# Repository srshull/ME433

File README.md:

# ME433
Homework and other files for ME 433 - Advanced Mechatronics, which I completed in the Spring quarter of 2016 at Northwestern University. 

## Final Project
Here's a sneak peek at my final project - a line following robot. The camera on an Android phone detects the line, then communicates with a PIC32 microcontroller over USB. The PIC32 implements a proportional-integral controller to control the two motors in order to follow the line around a track. I designed the chassis, motor mounts, and wheels in Onshape and fabricated them using a laser cutter and 3D printer, respectively.

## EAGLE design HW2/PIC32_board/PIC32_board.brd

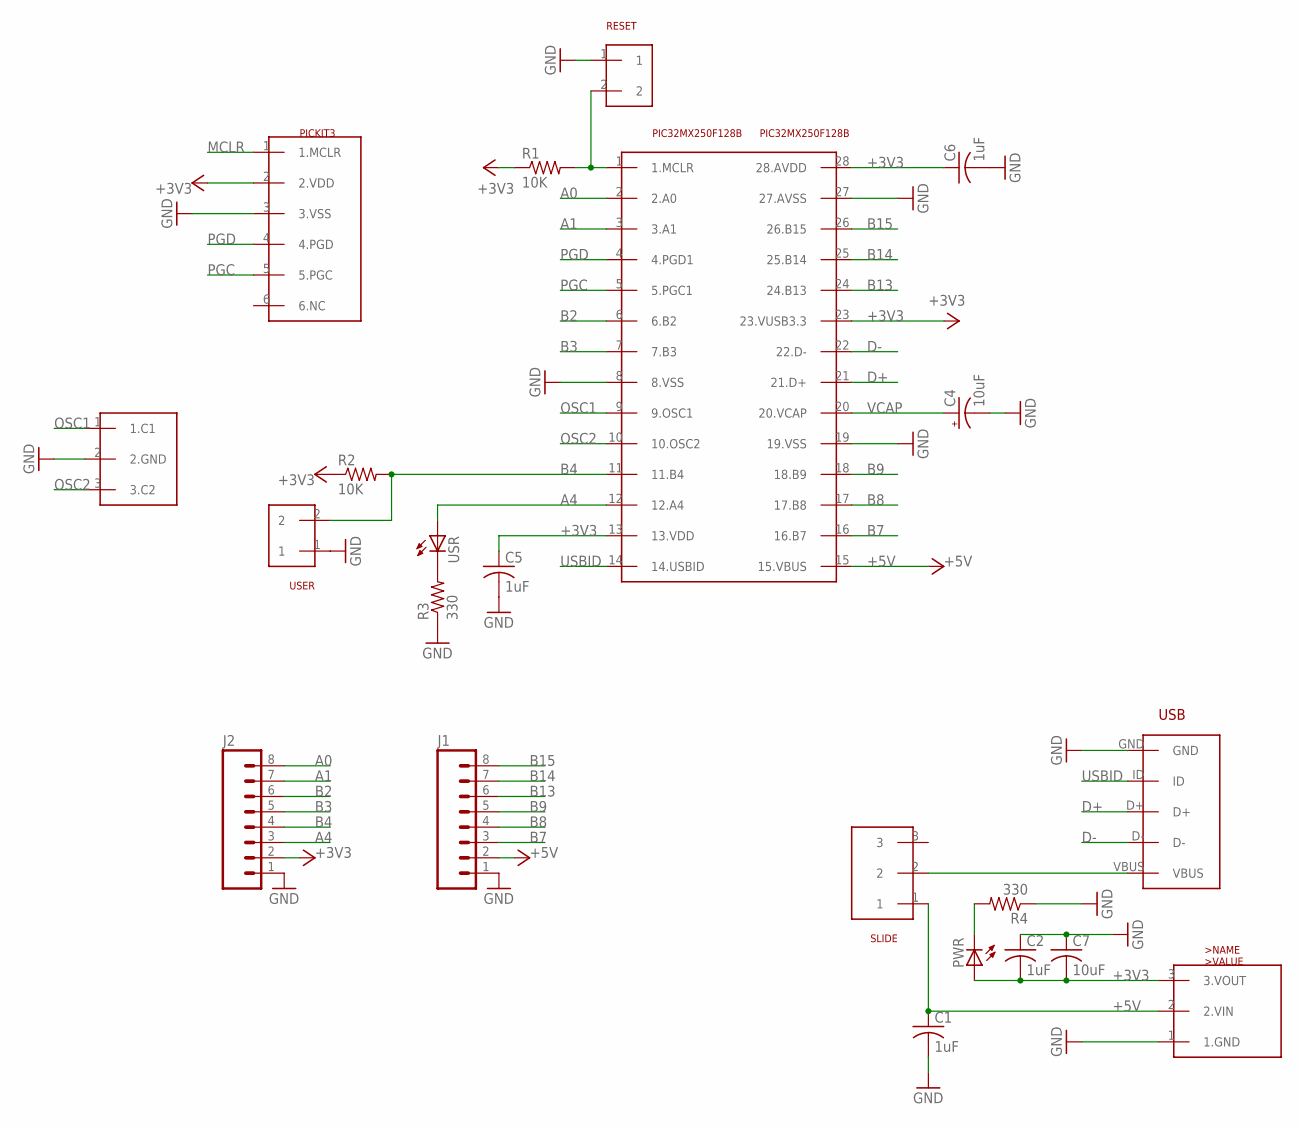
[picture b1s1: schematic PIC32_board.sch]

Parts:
C1, C2, C5, C6: 1uF; C025-024X044
C4: 10uF; B45181B
C7: 10uF; C025-024X044
J1, J2: M08; 1X08_ROUND
OSC: OSC; 1X03
PIC32MX250F128B: PIC32MX250F128B; DIL28-3
PICKIT3: PICKIT3; 1X06
PWR: LED3MM
R1, R2: 10K; 0207/10
R3, R4: 330; 0207/10
RESET: PUSHBUTTON
SLIDE: SLIDE
U$3: MCP1702; TO92
USB: USB_5PIN; USB-MB-H
USER: PUSHBUTTON
USR: LED3MM

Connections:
+3V3: C2.2, C5.1, C6.1, C7.2, J2.2, PIC32MX250F128B.13 (13.VDD), PIC32MX250F128B.23 (23.VUSB3.3), PIC32MX250F128B.28 (28.AVDD), PICKIT3.2 (2.VDD), PWR.A, R1.1, R2.1, U$3.3 (3.VOUT)
+5V: C1.1, J1.2, PIC32MX250F128B.15 (15.VBUS), SLIDE.1, U$3.2 (2.VIN)
A0: J2.8, PIC32MX250F128B.2 (2.A0)
A1: J2.7, PIC32MX250F128B.3 (3.A1)
A4: J2.3, PIC32MX250F128B.12 (12.A4), USR.A
B2: J2.6, PIC32MX250F128B.6 (6.B2)
B3: J2.5, PIC32MX250F128B.7 (7.B3)
B4: J2.4, PIC32MX250F128B.11 (11.B4), R2.2, USER.2
B7: J1.3, PIC32MX250F128B.16 (16.B7)
B8: J1.4, PIC32MX250F128B.17 (17.B8)
B9: J1.5, PIC32MX250F128B.18 (18.B9)
B13: J1.6, PIC32MX250F128B.24 (24.B13)
B14: J1.7, PIC32MX250F128B.25 (25.B14)
B15: J1.8, PIC32MX250F128B.26 (26.B15)
D+: PIC32MX250F128B.21 (21.D+), USB.D+
D-: PIC32MX250F128B.22 (22.D-), USB.D-
GND: C1.2, C2.1, C4.-, C5.2, C6.2, C7.1, J1.1, J2.1, OSC.2 (2.GND), PIC32MX250F128B.8 (8.VSS), PIC32MX250F128B.19 (19.VSS), PIC32MX250F128B.27 (27.AVSS), PICKIT3.3 (3.VSS), R3.1, R4.1, RESET.1, U$3.1 (1.GND), USB.GND, USER.1
MCLR: PIC32MX250F128B.1 (1.MCLR), PICKIT3.1 (1.MCLR), R1.2, RESET.2
unnamed: R3.2, USR.K (C)
unnamed: PWR.K (C), R4.2
unnamed: SLIDE.2, USB.VBUS
OSC1: OSC.1 (1.C1), PIC32MX250F128B.9 (9.OSC1)
OSC2: OSC.3 (3.C2), PIC32MX250F128B.10 (10.OSC2)
PGC: PIC32MX250F128B.5 (5.PGC1), PICKIT3.5 (5.PGC)
PGD: PIC32MX250F128B.4 (4.PGD1), PICKIT3.4 (4.PGD)
USBID: PIC32MX250F128B.14 (14.USBID), USB.ID
VCAP: C4.+, PIC32MX250F128B.20 (20.VCAP)

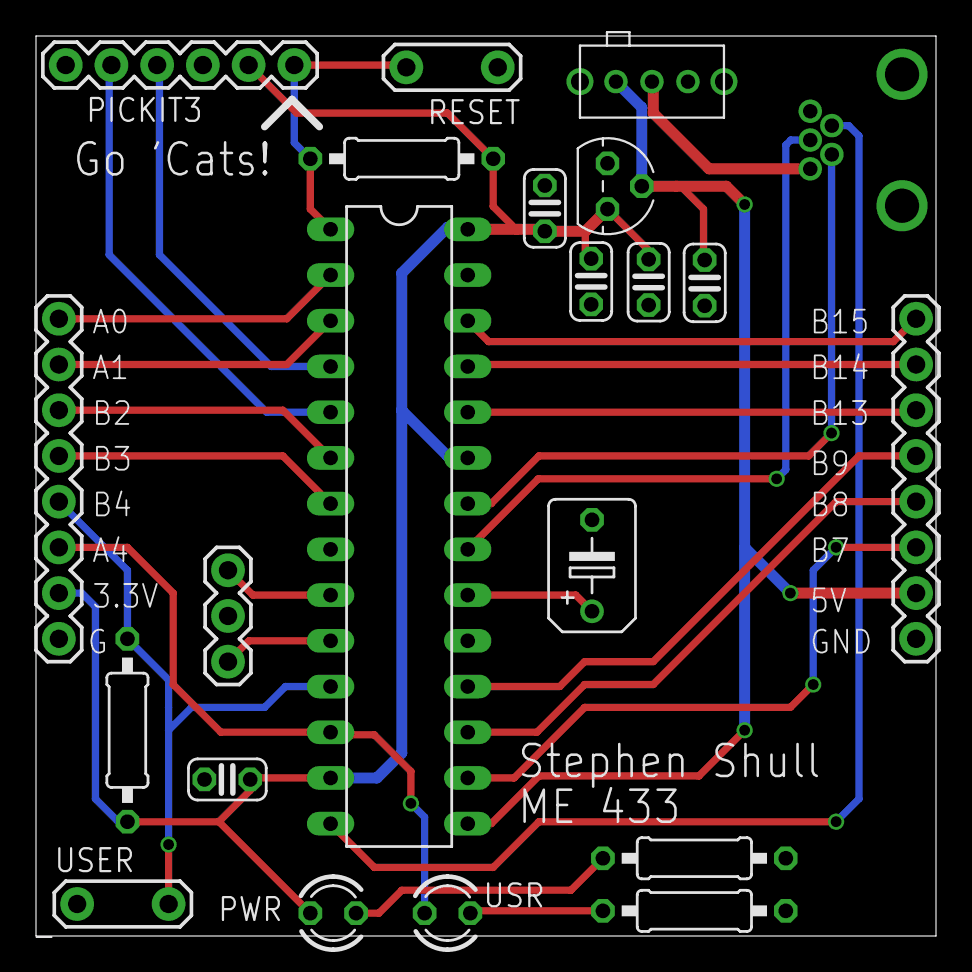
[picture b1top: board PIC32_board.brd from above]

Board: 2 copper layers, 50.0 x 50.0 mm, 22 parts (0 on the bottom side), 27 nets.

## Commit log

2016-04-01 added photo of scope showing oscillations
2016-04-01 test commit
2016-04-01 second test
2016-04-05 initial commit of HW1 project
2016-04-05 #PRAGMA values defined
2016-04-05 added picture of circuit
2016-04-05 added initializations for I/O pins
2016-04-05 Added light pulsing and button pausing
2016-04-14 Ready to be checked before order
2016-04-19 Initial commit of HW4. DAC working
2016-04-20 triangle wave working
2016-04-20 Moved all SPI stuff to new MCP4902 library
2016-04-30 got sine wave and pin expander working properly
2016-04-30 Added photo showing HW4 working
2016-05-03 initial commit of HW6 code. WHOAMI received properly
2016-05-04 PWM set up on OC1
2016-05-05 Initial commit - drawing a bar on the LCD
2016-05-05 writing strings to LCD works
2016-05-10 moved LCD character writing into library
2016-05-10 added check for valid pixel location
2016-05-24 CAD, DXF, and photo of laser cut box
2016-05-24 CAD, STL, and picture of 3D print
2016-05-24 Android hello world with slider
2016-06-05 added seekbar to adjust threshold
2016-06-05 CDC working, checked with screen
2016-06-07 racer PIC code
2016-06-09 cdc communication between PIC and android phone working
2016-06-09 USB mouse working in Y direction
2016-06-09 pictures and results (with video link)
2016-06-09 final android racer code
2016-06-09 final PIC racer code
2020-08-24 added gif of final project working
2020-08-24 added picture of final project
2020-08-24 Update README.md
    Added picture and video of line following final project
